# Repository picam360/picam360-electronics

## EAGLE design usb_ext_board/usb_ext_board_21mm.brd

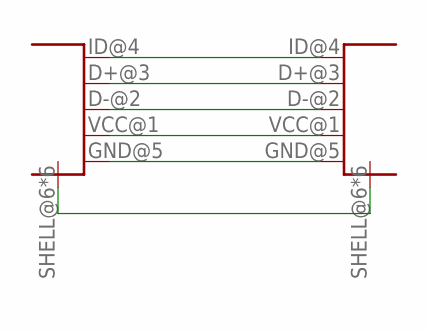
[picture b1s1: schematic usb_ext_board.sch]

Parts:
MALE1, MALE2: USB-ID; USB3150-30-130

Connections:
D+: MALE1.D+@3 (D+), MALE2.D+@3 (D+)
D-: MALE1.D-@2 (D-), MALE2.D-@2 (D-)
GND: MALE1.GND@5 (GND), MALE1.SHELL@6 (SHELL), MALE1.SHELL@7 (SHELL), MALE1.SHELL@8 (SHELL), MALE1.SHELL@9 (SHELL), MALE1.SHELL@10 (SHELL), MALE1.SHELL@11 (SHELL), MALE2.GND@5 (GND), MALE2.SHELL@6 (SHELL), MALE2.SHELL@7 (SHELL), MALE2.SHELL@8 (SHELL), MALE2.SHELL@9 (SHELL), MALE2.SHELL@10 (SHELL), MALE2.SHELL@11 (SHELL)
ID: MALE1.ID@4 (ID), MALE2.ID@4 (ID)
VCC: MALE1.VCC@1 (VBUS), MALE2.VCC@1 (VBUS)

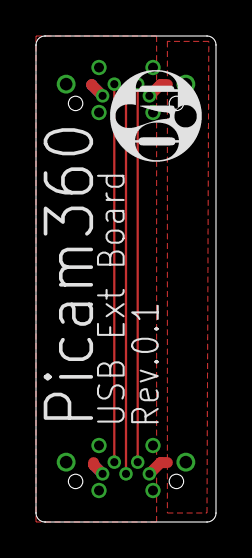
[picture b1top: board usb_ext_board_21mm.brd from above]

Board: 2 copper layers, 10.0 x 27.0 mm, 3 parts (0 on the bottom side), 5 nets.

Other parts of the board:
LOGO1: OHMYDIGIFAB_LOGO
